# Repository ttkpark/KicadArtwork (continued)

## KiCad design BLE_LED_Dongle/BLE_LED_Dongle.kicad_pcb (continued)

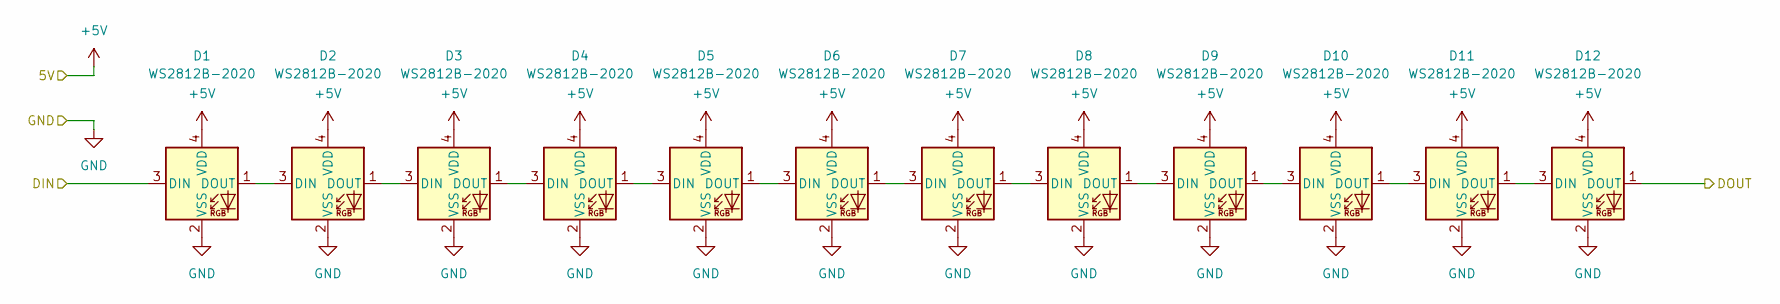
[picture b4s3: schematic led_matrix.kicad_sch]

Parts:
D1, D2, D3, D4, D5, D6, D7, D8, D9, D10, D11, D12: WS2812B-2020; LED_WS2812B-2020_PLCC4_2.0x2.0mm; LCSC C965555

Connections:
+5V: D1.4 (VDD), D2.4 (VDD), D3.4 (VDD), D4.4 (VDD), D5.4 (VDD), D6.4 (VDD), D7.4 (VDD), D8.4 (VDD), D9.4 (VDD), D10.4 (VDD), D11.4 (VDD), D12.4 (VDD); also elsewhere on the board
/LED_Matrix1/DIN: D1.3 (DIN); also elsewhere on the board
/LED_Matrix1/LED_Matrix_Line0/DOUT: D12.1 (DOUT); also elsewhere on the board
GND: D1.2 (VSS), D2.2 (VSS), D3.2 (VSS), D4.2 (VSS), D5.2 (VSS), D6.2 (VSS), D7.2 (VSS), D8.2 (VSS), D9.2 (VSS), D10.2 (VSS), D11.2 (VSS), D12.2 (VSS); also elsewhere on the board
unnamed: D1.1 (DOUT), D2.3 (DIN)
unnamed: D2.1 (DOUT), D3.3 (DIN)
unnamed: D3.1 (DOUT), D4.3 (DIN)
unnamed: D4.1 (DOUT), D5.3 (DIN)
unnamed: D5.1 (DOUT), D6.3 (DIN)
unnamed: D6.1 (DOUT), D7.3 (DIN)
unnamed: D7.1 (DOUT), D8.3 (DIN)
unnamed: D8.1 (DOUT), D9.3 (DIN)
unnamed: D9.1 (DOUT), D10.3 (DIN)
unnamed: D10.1 (DOUT), D11.3 (DIN)
unnamed: D11.1 (DOUT), D12.3 (DIN)

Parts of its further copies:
D13, D14, D15, D16, D17, D18, D19, D20, D21, D22, D23, D24, D25, D26, D27, D28, D29, D30, D31, D32, D33, D34, D35, D36, D37, D38, D39, D40, D41, D42, D43, D44, D45, D46, D47, D48, D49, D50, D51, D52, D53, D54, D55, D56, D57, D58, D59, D60, D61, D62, D63, D64, D65, D66, D67, D68, D69, D70, D71, D72, D73, D74, D75, D76, D77, D78, D79, D80, D81, D82, D83, D84, D85, D86, D87, D88, D89, D90, D91, D92, D93, D94, D95, D96, D97, D98, D99, D100, D101, D102, D103, D104, D105, D106, D107, D108, D109, D110, D111, D112, D113, D114, D115, D116, D117, D118, D119, D120, D121, D122, D123, D124, D125, D126, D127, D128, D129, D130, D131, D132, D133, D134, D135, D136, D137, D138, D139, D140, D141, D142, D143, D144: WS2812B-2020; LED_WS2812B-2020_PLCC4_2.0x2.0mm; LCSC C965555

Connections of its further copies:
+5V: D13.4 (VDD), D14.4 (VDD), D15.4 (VDD), D16.4 (VDD), D17.4 (VDD), D18.4 (VDD), D19.4 (VDD), D20.4 (VDD), D21.4 (VDD), D22.4 (VDD), D23.4 (VDD), D24.4 (VDD), D25.4 (VDD), D26.4 (VDD), D27.4 (VDD), D28.4 (VDD), D29.4 (VDD), D30.4 (VDD), D31.4 (VDD), D32.4 (VDD), D33.4 (VDD), D34.4 (VDD), D35.4 (VDD), D36.4 (VDD), D37.4 (VDD), D38.4 (VDD), D39.4 (VDD), D40.4 (VDD), D41.4 (VDD), D42.4 (VDD), D43.4 (VDD), D44.4 (VDD), D45.4 (VDD), D46.4 (VDD), D47.4 (VDD), D48.4 (VDD), D49.4 (VDD), D50.4 (VDD), D51.4 (VDD), D52.4 (VDD), D53.4 (VDD), D54.4 (VDD), D55.4 (VDD), D56.4 (VDD), D57.4 (VDD), D58.4 (VDD), D59.4 (VDD), D60.4 (VDD), D61.4 (VDD), D62.4 (VDD), D63.4 (VDD), D64.4 (VDD), D65.4 (VDD), D66.4 (VDD), D67.4 (VDD), D68.4 (VDD), D69.4 (VDD), D70.4 (VDD), D71.4 (VDD), D72.4 (VDD), D73.4 (VDD), D74.4 (VDD), D75.4 (VDD), D76.4 (VDD), D77.4 (VDD), D78.4 (VDD), D79.4 (VDD), D80.4 (VDD), D81.4 (VDD), D82.4 (VDD), D83.4 (VDD), D84.4 (VDD), D85.4 (VDD), D86.4 (VDD), D87.4 (VDD), D88.4 (VDD), D89.4 (VDD), D90.4 (VDD), D91.4 (VDD), D92.4 (VDD), D93.4 (VDD), D94.4 (VDD), D95.4 (VDD), D96.4 (VDD), D97.4 (VDD), D98.4 (VDD), D99.4 (VDD), D100.4 (VDD), D101.4 (VDD), D102.4 (VDD), D103.4 (VDD), D104.4 (VDD), D105.4 (VDD), D106.4 (VDD), D107.4 (VDD), D108.4 (VDD), D109.4 (VDD), D110.4 (VDD), D111.4 (VDD), D112.4 (VDD), D113.4 (VDD), D114.4 (VDD), D115.4 (VDD), D116.4 (VDD), D117.4 (VDD), D118.4 (VDD), D119.4 (VDD), D120.4 (VDD), D121.4 (VDD), D122.4 (VDD), D123.4 (VDD), D124.4 (VDD), D125.4 (VDD), D126.4 (VDD), D127.4 (VDD), D128.4 (VDD), D129.4 (VDD), D130.4 (VDD), D131.4 (VDD), D132.4 (VDD), D133.4 (VDD), D134.4 (VDD), D135.4 (VDD), D136.4 (VDD), D137.4 (VDD), D138.4 (VDD), D139.4 (VDD), D140.4 (VDD), D141.4 (VDD), D142.4 (VDD), D143.4 (VDD), D144.4 (VDD); also elsewhere on the board
/LED_Matrix1/LED_Matrix_Line0/DOUT: D13.3 (DIN); also elsewhere on the board
/LED_Matrix1/LED_Matrix_Line1/DOUT: D24.1 (DOUT), D25.3 (DIN)
/LED_Matrix1/LED_Matrix_Line2/DOUT: D36.1 (DOUT), D37.3 (DIN)
/LED_Matrix1/LED_Matrix_Line3/DOUT: D48.1 (DOUT), D49.3 (DIN)
/LED_Matrix1/LED_Matrix_Line4/DOUT: D60.1 (DOUT), D61.3 (DIN)
/LED_Matrix1/LED_Matrix_Line5/DOUT: D72.1 (DOUT), D73.3 (DIN)
/LED_Matrix1/LED_Matrix_Line6/DOUT: D84.1 (DOUT), D85.3 (DIN)
/LED_Matrix1/LED_Matrix_Line7/DOUT: D96.1 (DOUT), D97.3 (DIN)
/LED_Matrix1/LED_Matrix_Line8/DOUT: D108.1 (DOUT), D109.3 (DIN)
/LED_Matrix1/LED_Matrix_Line10/DIN: D120.1 (DOUT), D121.3 (DIN)
/LED_Matrix1/LED_Matrix_Line10/DOUT: D132.1 (DOUT), D133.3 (DIN)
/LED_Matrix1/LED_Matrix_Line11/DOUT: D144.1 (DOUT)
GND: D13.2 (VSS), D14.2 (VSS), D15.2 (VSS), D16.2 (VSS), D17.2 (VSS), D18.2 (VSS), D19.2 (VSS), D20.2 (VSS), D21.2 (VSS), D22.2 (VSS), D23.2 (VSS), D24.2 (VSS), D25.2 (VSS), D26.2 (VSS), D27.2 (VSS), D28.2 (VSS), D29.2 (VSS), D30.2 (VSS), D31.2 (VSS), D32.2 (VSS), D33.2 (VSS), D34.2 (VSS), D35.2 (VSS), D36.2 (VSS), D37.2 (VSS), D38.2 (VSS), D39.2 (VSS), D40.2 (VSS), D41.2 (VSS), D42.2 (VSS), D43.2 (VSS), D44.2 (VSS), D45.2 (VSS), D46.2 (VSS), D47.2 (VSS), D48.2 (VSS), D49.2 (VSS), D50.2 (VSS), D51.2 (VSS), D52.2 (VSS), D53.2 (VSS), D54.2 (VSS), D55.2 (VSS), D56.2 (VSS), D57.2 (VSS), D58.2 (VSS), D59.2 (VSS), D60.2 (VSS), D61.2 (VSS), D62.2 (VSS), D63.2 (VSS), D64.2 (VSS), D65.2 (VSS), D66.2 (VSS), D67.2 (VSS), D68.2 (VSS), D69.2 (VSS), D70.2 (VSS), D71.2 (VSS), D72.2 (VSS), D73.2 (VSS), D74.2 (VSS), D75.2 (VSS), D76.2 (VSS), D77.2 (VSS), D78.2 (VSS), D79.2 (VSS), D80.2 (VSS), D81.2 (VSS), D82.2 (VSS), D83.2 (VSS), D84.2 (VSS), D85.2 (VSS), D86.2 (VSS), D87.2 (VSS), D88.2 (VSS), D89.2 (VSS), D90.2 (VSS), D91.2 (VSS), D92.2 (VSS), D93.2 (VSS), D94.2 (VSS), D95.2 (VSS), D96.2 (VSS), D97.2 (VSS), D98.2 (VSS), D99.2 (VSS), D100.2 (VSS), D101.2 (VSS), D102.2 (VSS), D103.2 (VSS), D104.2 (VSS), D105.2 (VSS), D106.2 (VSS), D107.2 (VSS), D108.2 (VSS), D109.2 (VSS), D110.2 (VSS), D111.2 (VSS), D112.2 (VSS), D113.2 (VSS), D114.2 (VSS), D115.2 (VSS), D116.2 (VSS), D117.2 (VSS), D118.2 (VSS), D119.2 (VSS), D120.2 (VSS), D121.2 (VSS), D122.2 (VSS), D123.2 (VSS), D124.2 (VSS), D125.2 (VSS), D126.2 (VSS), D127.2 (VSS), D128.2 (VSS), D129.2 (VSS), D130.2 (VSS), D131.2 (VSS), D132.2 (VSS), D133.2 (VSS), D134.2 (VSS), D135.2 (VSS), D136.2 (VSS), D137.2 (VSS), D138.2 (VSS), D139.2 (VSS), D140.2 (VSS), D141.2 (VSS), D142.2 (VSS), D143.2 (VSS), D144.2 (VSS); also elsewhere on the board
unnamed: D13.1 (DOUT), D14.3 (DIN)
unnamed: D14.1 (DOUT), D15.3 (DIN)
unnamed: D15.1 (DOUT), D16.3 (DIN)
unnamed: D16.1 (DOUT), D17.3 (DIN)
unnamed: D17.1 (DOUT), D18.3 (DIN)
unnamed: D18.1 (DOUT), D19.3 (DIN)
unnamed: D19.1 (DOUT), D20.3 (DIN)
unnamed: D20.1 (DOUT), D21.3 (DIN)
unnamed: D21.1 (DOUT), D22.3 (DIN)
unnamed: D22.1 (DOUT), D23.3 (DIN)
unnamed: D23.1 (DOUT), D24.3 (DIN)
unnamed: D25.1 (DOUT), D26.3 (DIN)
unnamed: D26.1 (DOUT), D27.3 (DIN)
unnamed: D27.1 (DOUT), D28.3 (DIN)
unnamed: D28.1 (DOUT), D29.3 (DIN)
unnamed: D29.1 (DOUT), D30.3 (DIN)
unnamed: D30.1 (DOUT), D31.3 (DIN)
unnamed: D31.1 (DOUT), D32.3 (DIN)
unnamed: D32.1 (DOUT), D33.3 (DIN)
unnamed: D33.1 (DOUT), D34.3 (DIN)
unnamed: D34.1 (DOUT), D35.3 (DIN)
unnamed: D35.1 (DOUT), D36.3 (DIN)
unnamed: D37.1 (DOUT), D38.3 (DIN)
unnamed: D38.1 (DOUT), D39.3 (DIN)
unnamed: D39.1 (DOUT), D40.3 (DIN)
unnamed: D40.1 (DOUT), D41.3 (DIN)
unnamed: D41.1 (DOUT), D42.3 (DIN)
unnamed: D42.1 (DOUT), D43.3 (DIN)
unnamed: D43.1 (DOUT), D44.3 (DIN)
unnamed: D44.1 (DOUT), D45.3 (DIN)
unnamed: D45.1 (DOUT), D46.3 (DIN)
unnamed: D46.1 (DOUT), D47.3 (DIN)
unnamed: D47.1 (DOUT), D48.3 (DIN)
unnamed: D49.1 (DOUT), D50.3 (DIN)
unnamed: D50.1 (DOUT), D51.3 (DIN)
unnamed: D51.1 (DOUT), D52.3 (DIN)
unnamed: D52.1 (DOUT), D53.3 (DIN)
unnamed: D53.1 (DOUT), D54.3 (DIN)
unnamed: D54.1 (DOUT), D55.3 (DIN)
unnamed: D55.1 (DOUT), D56.3 (DIN)
unnamed: D56.1 (DOUT), D57.3 (DIN)
unnamed: D57.1 (DOUT), D58.3 (DIN)
unnamed: D58.1 (DOUT), D59.3 (DIN)
unnamed: D59.1 (DOUT), D60.3 (DIN)
unnamed: D61.1 (DOUT), D62.3 (DIN)
unnamed: D62.1 (DOUT), D63.3 (DIN)
unnamed: D63.1 (DOUT), D64.3 (DIN)
unnamed: D64.1 (DOUT), D65.3 (DIN)
unnamed: D65.1 (DOUT), D66.3 (DIN)
unnamed: D66.1 (DOUT), D67.3 (DIN)
unnamed: D67.1 (DOUT), D68.3 (DIN)
unnamed: D68.1 (DOUT), D69.3 (DIN)
unnamed: D69.1 (DOUT), D70.3 (DIN)
unnamed: D70.1 (DOUT), D71.3 (DIN)
unnamed: D71.1 (DOUT), D72.3 (DIN)
unnamed: D73.1 (DOUT), D74.3 (DIN)
unnamed: D74.1 (DOUT), D75.3 (DIN)
unnamed: D75.1 (DOUT), D76.3 (DIN)
unnamed: D76.1 (DOUT), D77.3 (DIN)
unnamed: D77.1 (DOUT), D78.3 (DIN)
unnamed: D78.1 (DOUT), D79.3 (DIN)
unnamed: D79.1 (DOUT), D80.3 (DIN)
unnamed: D80.1 (DOUT), D81.3 (DIN)
unnamed: D81.1 (DOUT), D82.3 (DIN)
unnamed: D82.1 (DOUT), D83.3 (DIN)
unnamed: D83.1 (DOUT), D84.3 (DIN)
unnamed: D85.1 (DOUT), D86.3 (DIN)
unnamed: D86.1 (DOUT), D87.3 (DIN)
unnamed: D87.1 (DOUT), D88.3 (DIN)
unnamed: D88.1 (DOUT), D89.3 (DIN)
unnamed: D89.1 (DOUT), D90.3 (DIN)
unnamed: D90.1 (DOUT), D91.3 (DIN)
unnamed: D91.1 (DOUT), D92.3 (DIN)
unnamed: D92.1 (DOUT), D93.3 (DIN)
unnamed: D93.1 (DOUT), D94.3 (DIN)
unnamed: D94.1 (DOUT), D95.3 (DIN)
unnamed: D95.1 (DOUT), D96.3 (DIN)
unnamed: D97.1 (DOUT), D98.3 (DIN)
unnamed: D98.1 (DOUT), D99.3 (DIN)
unnamed: D99.1 (DOUT), D100.3 (DIN)
unnamed: D100.1 (DOUT), D101.3 (DIN)
unnamed: D101.1 (DOUT), D102.3 (DIN)
unnamed: D102.1 (DOUT), D103.3 (DIN)
unnamed: D103.1 (DOUT), D104.3 (DIN)
unnamed: D104.1 (DOUT), D105.3 (DIN)
unnamed: D105.1 (DOUT), D106.3 (DIN)
unnamed: D106.1 (DOUT), D107.3 (DIN)
unnamed: D107.1 (DOUT), D108.3 (DIN)
unnamed: D109.1 (DOUT), D110.3 (DIN)
unnamed: D110.1 (DOUT), D111.3 (DIN)
unnamed: D111.1 (DOUT), D112.3 (DIN)
unnamed: D112.1 (DOUT), D113.3 (DIN)
unnamed: D113.1 (DOUT), D114.3 (DIN)
unnamed: D114.1 (DOUT), D115.3 (DIN)
unnamed: D115.1 (DOUT), D116.3 (DIN)
unnamed: D116.1 (DOUT), D117.3 (DIN)
unnamed: D117.1 (DOUT), D118.3 (DIN)
unnamed: D118.1 (DOUT), D119.3 (DIN)
unnamed: D119.1 (DOUT), D120.3 (DIN)
unnamed: D121.1 (DOUT), D122.3 (DIN)
unnamed: D122.1 (DOUT), D123.3 (DIN)
unnamed: D123.1 (DOUT), D124.3 (DIN)
unnamed: D124.1 (DOUT), D125.3 (DIN)
unnamed: D125.1 (DOUT), D126.3 (DIN)
unnamed: D126.1 (DOUT), D127.3 (DIN)
unnamed: D127.1 (DOUT), D128.3 (DIN)
unnamed: D128.1 (DOUT), D129.3 (DIN)
unnamed: D129.1 (DOUT), D130.3 (DIN)
unnamed: D130.1 (DOUT), D131.3 (DIN)
unnamed: D131.1 (DOUT), D132.3 (DIN)
unnamed: D133.1 (DOUT), D134.3 (DIN)
unnamed: D134.1 (DOUT), D135.3 (DIN)
unnamed: D135.1 (DOUT), D136.3 (DIN)
unnamed: D136.1 (DOUT), D137.3 (DIN)
unnamed: D137.1 (DOUT), D138.3 (DIN)
unnamed: D138.1 (DOUT), D139.3 (DIN)
unnamed: D139.1 (DOUT), D140.3 (DIN)
unnamed: D140.1 (DOUT), D141.3 (DIN)
unnamed: D141.1 (DOUT), D142.3 (DIN)
unnamed: D142.1 (DOUT), D143.3 (DIN)
unnamed: D143.1 (DOUT), D144.3 (DIN)

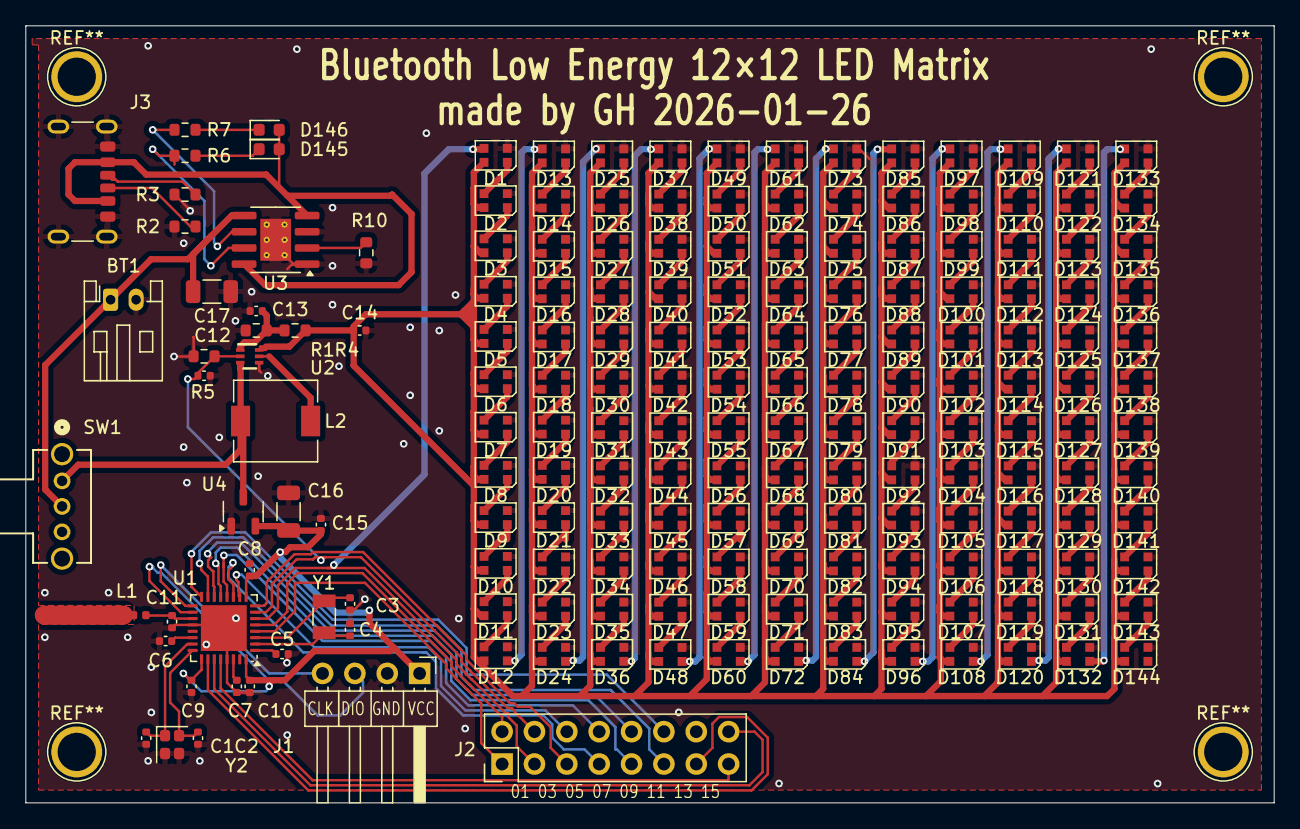
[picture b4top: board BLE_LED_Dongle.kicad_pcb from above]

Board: 2 copper layers, 98.0 x 61.0 mm, 184 parts (0 on the bottom side), 183 nets.

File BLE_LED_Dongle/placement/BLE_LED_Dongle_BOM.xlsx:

Value | Reference | LCSC | Footprint
3.7V | BT1 | C295747 | Connector_JST:JST_PH_S2B-PH-K_1x02_P2.00mm_Horizontal
12p | C1,C2,C3,C4 | C76948 | Capacitor_SMD:C_0402_1005Metric
100n | C5,C8,C9,C15 | C1525 | Capacitor_SMD:C_0402_1005Metric
100p | C6 | C26409 | Capacitor_SMD:C_0402_1005Metric
1u | C7,C12,C14 | C14445 | Capacitor_SMD:C_0402_1005Metric
4u7 | C10 | C23733 | Capacitor_SMD:C_0402_1005Metric
0.8p | C11 | C327032 | Capacitor_SMD:C_0402_1005Metric
22n | C13 | C337699 | Capacitor_SMD:C_0402_1005Metric
47u | C16,C17 | C68361 | Capacitor_SMD:C_1206_3216Metric
WS2812B-2020 | D1,D2,D3,D4,D5,D6,D7,D8,D9,D10,D11,D12,D13,D14,D15,D16,D17,D18,D19,D20,D21,D22,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 | C965555 | LED_SMD:LED_WS2812B-2020_PLCC4_2.0x2.0mm
Charge | D145 | C19171390 | LED_SMD:LED_0603_1608Metric
Standby | D146 | C22371297 | LED_SMD:LED_0603_1608Metric
Conn_01x04 | J1 | C492412 | Connector_PinHeader_2.54mm:PinHeader_1x04_P2.54mm_Horizontal
Conn_02x08_Counter_Clockwise | J2 |  | Connector_PinHeader_2.54mm:PinHeader_2x08_P2.54mm_Vertical
USB_C_Receptacle_PowerOnly_6P | J3 | C668623 | Connector_USB:USB_C_Receptacle_GCT_USB4125-xx-x-0190_6P_TopMnt_Horizontal
3n9 | L1 | C98062 | Inductor_SMD:L_0402_1005Metric
1u | L2 | C5343973 | Inductor_SMD:L_6.3x6.3_H3
1K5 | R1,R5,R6,R7,R10 | C22843 | Resistor_SMD:R_0603_1608Metric
5K1 | R2,R3 | C23186 | Resistor_SMD:R_0603_1608Metric
11K | R4 | C2906986 | Resistor_SMD:R_0603_1608Metric
SW_SPDT | SW1 | C431547 | SK12D07VG4NSPA_CNK
nRF52810-QCxx | U1 | C519278 | Package_DFN_QFN:QFN-32-1EP_5x5mm_P0.5mm_EP3.6x3.6mm
TPS61023DRLR | U2 | C919459 | DRL0006A
TP4056-42-ESOP8 | U3 | C382139 | Package_SO:SOIC-8-1EP_3.9x4.9mm_P1.27mm_EP2.41x3.3mm_ThermalVias
XC6206PxxxMR | U4 | C5446 | Package_TO_SOT_SMD:SOT-23-3
Crystal | Y1 | C97606 | Crystal:Crystal_SMD_3215-2Pin_3.2x1.5mm
Crystal_GND23 | Y2 | C2965582 | Crystal:Crystal_SMD_2016-4Pin_2.0x1.6mm

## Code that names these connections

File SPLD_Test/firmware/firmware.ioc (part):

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Mcu.Name=STM32F030K6Tx
Mcu.Package=LQFP32
Mcu.UserName=STM32F030K6Tx
PA10.GPIOParameters=GPIO_Label
PA10.GPIO_Label=CPLD_IO31
PA10.Signal=GPIO_Input
PA11.Signal=S_TIM1_CH4
PA12.GPIOParameters=GPIO_Label
PA12.GPIO_Label=CPLD_IO34
PA12.Signal=GPIO_Input
PA13.Mode=Serial_Wire
PA13.Signal=SYS_SWDIO
PA14.Mode=Serial_Wire
PA14.Signal=SYS_SWCLK
PA15.GPIOParameters=GPIO_Label
PA15.GPIO_Label=CPLD_IO37
PA15.Signal=GPIO_Input
PA2.GPIOParameters=GPIO_Label
PA2.GPIO_Label=CPLD_IO28
PA2.Signal=GPIO_Input
PA3.GPIOParameters=GPIO_Label
PA3.GPIO_Label=CPLD_IO29
PA3.Signal=GPIO_Input
PA4.GPIOParameters=GPIO_Label
PA4.GPIO_Label=OLED_NSS
PA4.Signal=GPIO_Output
PA5.Mode=Full_Duplex_Master
PA5.Signal=SPI1_SCK
PA6.Mode=Full_Duplex_Master
PA6.Signal=SPI1_MISO
PA7.Mode=Full_Duplex_Master
PA7.Signal=SPI1_MOSI
PA8.GPIOParameters=GPIO_Label
PA8.GPIO_Label=OLED_RST
PA8.Signal=GPIO_Output
PA9.GPIOParameters=GPIO_Label
PA9.GPIO_Label=OLED_DC
PA9.Signal=GPIO_Output
PB6.Mode=I2C
PB6.Signal=I2C1_SCL
PB7.Mode=I2C
PB7.Signal=I2C1_SDA
board=custom

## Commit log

2026-01-25 progress: PCB Part Placement of Patterns Complete
2026-01-27 progress: board 1 complete, board 2 schematics in progress.
2026-01-27 progress: CPLD Circuit schmatics complete & pattern placement in progress
2026-01-27 progress: CPLD Board complete
2026-01-28 start: project 3 started
2026-01-28 progress: previous project kalimba moved
2026-01-28 progress: pc kproject kalimba led placed
2026-02-05 smartbox_v2 start
2026-02-13 progress: CPLD Big Change
2026-02-14 0215 artwork
2026-02-17 0218 artwork
2026-02-23 0223 firmware dev
2026-02-23 0223 : stm32 complete CPLD in progress
2026-02-26 0224 : CPLD first success
2026-03-06 0307 CPLD complete
2026-03-30 0330 : SPLDTest save
